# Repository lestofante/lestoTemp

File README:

# lestoTemp 

This project is born to provide a quick and easy way to make a WiFi temperature sensor that can live many monts on a couple of AA battery.  
  
ESP8622-12E is used for v1 since this is what I got home, but later revision may switch to an ESP32.  
  
To simplify the schematics I chose to avoid the usage of any power regulator and use direct ~3v from the battery.    
  
Deep sleep will be used, with poeriodic wake up (current estimate, 10min), a measurement is taken and stored;  
to furter reduce power usage, the transmission will happer only once for day.
  
There will be OTA update support, and server will be minimal and self contained, probably I will use a rasperry, or maybe another ESP with and SD card.

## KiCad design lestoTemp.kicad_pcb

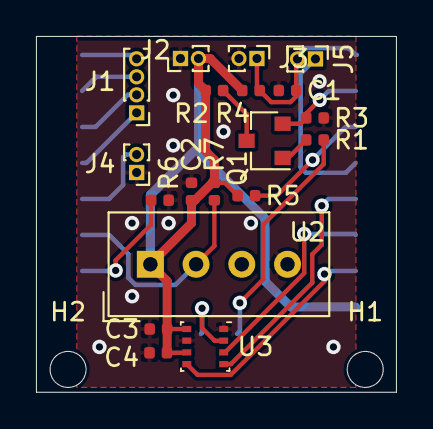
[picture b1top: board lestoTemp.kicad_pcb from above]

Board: 2 copper layers, 20.0 x 19.8 mm, 22 parts (1 on the bottom side), 20 nets.

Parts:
C1, C2: 100nF; C_0402_1005Metric
C3, C4: 100nf; C_0402_1005Metric
H1, H2: MountingHole; MountingHole_2mm
J1: PRG; PinHeader_1x04_P1.00mm_Vertical
J2: PWR; PinHeader_1x02_P1.00mm_Vertical
J3: RST; PinHeader_1x02_P1.00mm_Vertical
J4: PRG; PinHeader_1x02_P1.00mm_Vertical
J5: SLP; PinHeader_1x02_P1.00mm_Vertical
Q1: Q_NPN_BCE; SOT-23
R1, R5, R6: 1K; R_0402_1005Metric
R2: 33K; R_0402_1005Metric
R3, R4: 10K; R_0402_1005Metric
R7: 4.7K; R_0402_1005Metric
U1: ESP-12E
U2: DHT11; Aosong_DHT11_5.5x12.0_P2.54mm
U3: BME280; Bosch_LGA-8_2.5x2.5mm_P0.65mm_ClockwisePinNumbering

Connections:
+3V3: C2.1, C3.1, C4.1, J2.2, R2.1, R4.1, R5.1, R7.1, U1.8, U2.1, U3.6, U3.8
ADC: Q1.2, R3.1, U1.2
CLK: U1.5, U3.4
CS: U1.12, U3.2
ENABLE: R5.2, U1.3
GND: C1.2, C2.2, C3.2, C4.2, J2.1, J3.2, J4.1, R3.2, R6.2, U1.15, U2.4, U3.1, U3.7
GPIO0: J4.2, U1.18
GPIO2: R7.2, U1.17, U2.2
GPIO14: R1.1, U1.11
GPIO15: R6.1, U1.16
GPIO16: J5.1, U1.4
unnamed: J1.1, U1.19
unnamed: J1.2, U1.20
unnamed: J1.3, U1.21
unnamed: J1.4, U1.22
unnamed: Q1.1, R1.2
unnamed: Q1.3, R2.2
RESET: C1.1, J3.1, J5.2, R4.2, U1.1
SDI: U1.7, U3.5
SDO: U1.6, U3.3

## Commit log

2020-07-17 added readme
2020-08-01 added experimental source code
2020-08-01 fixed spi for V2, numerous pin changess
2020-08-02 varisu code fix
2020-08-02 added missing AP connection, and some other stuff
2021-01-09 Updated to work on esp32
    broken esp8266
2021-01-09 added missing files
